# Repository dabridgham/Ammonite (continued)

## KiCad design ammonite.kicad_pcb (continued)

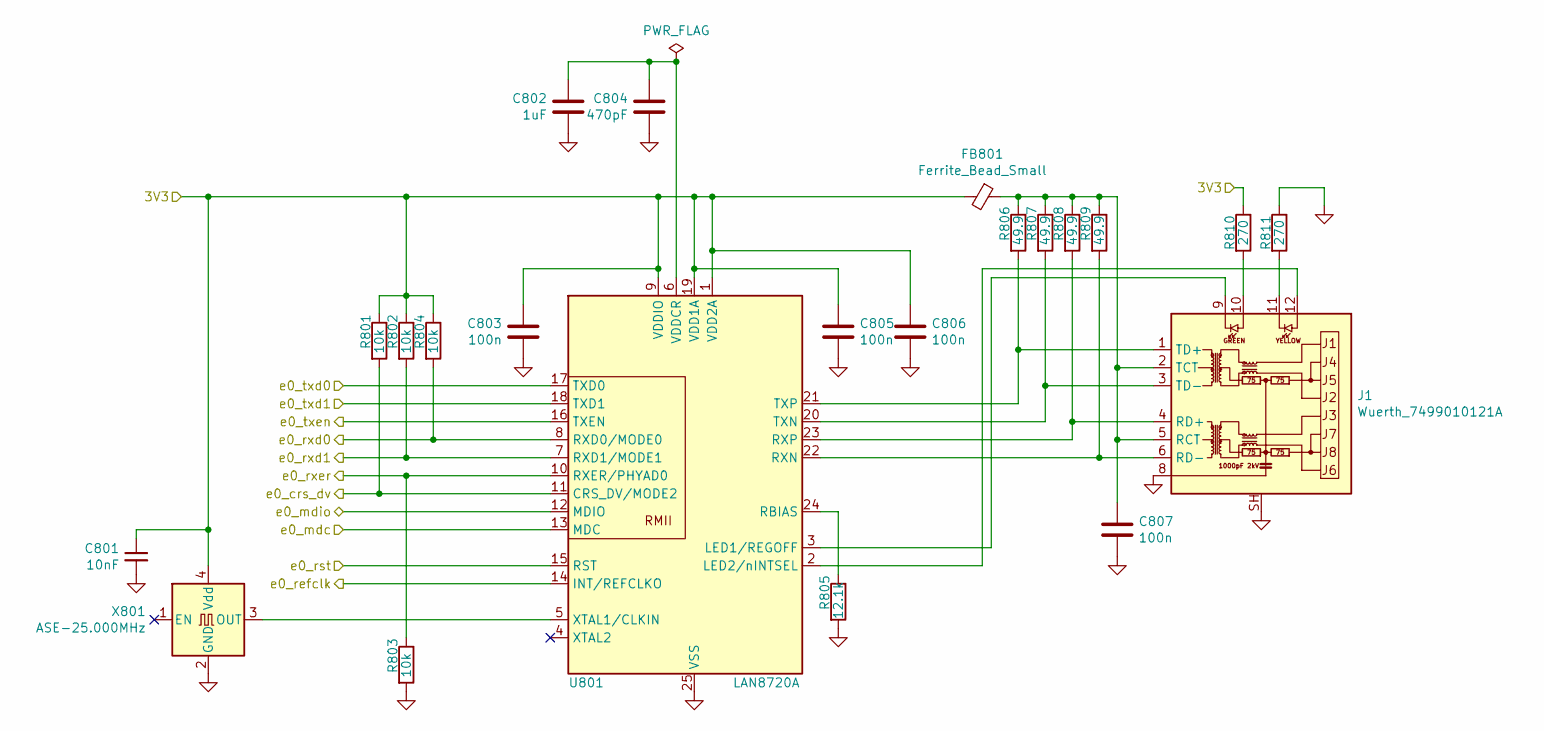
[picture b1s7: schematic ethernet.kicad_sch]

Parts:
C801: 10nF; C_0603_1608Metric
C802: 1uF; C_0603_1608Metric
C803, C805, C806, C807: 100n; C_0603_1608Metric
C804: 470pF; C_0603_1608Metric
FB801: Ferrite_Bead_Small; L_0603_1608Metric
J1: Wuerth_7499010121A; RJ45_Wuerth_7499010121A_Horizontal
R801, R802, R803, R804: 10k; R_0603_1608Metric
R805: 12.1k; R_0603_1608Metric
R806, R807, R808, R809: 49.9; R_0603_1608Metric
R810, R811: 270; R_0603_1608Metric
U801: LAN8720A; QFN-24-1EP_4x4mm_P0.5mm_EP2.6x2.6mm
X801: ASE-25.000MHz; Oscillator_SMD_Abracon_ASE-4Pin_3.2x2.5mm

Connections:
/3V3: C801.1, C803.1, C805.1, C806.1, FB801.2, R801.1, R802.1, R804.1, R810.1, U801.1 (VDD2A), U801.9 (VDDIO), U801.19 (VDD1A), X801.4 (Vdd); also elsewhere on the board
/e0_crs_dv: R801.2, U801.11 (CRS_DV/MODE2); also elsewhere on the board
/e0_mdc: U801.13 (MDC); also elsewhere on the board
/e0_mdio: U801.12 (MDIO); also elsewhere on the board
/e0_refclk: U801.14 (INT/REFCLKO); also elsewhere on the board
/e0_rst: U801.15 (RST); also elsewhere on the board
/e0_rxd0: R804.2, U801.8 (RXD0/MODE0); also elsewhere on the board
/e0_rxd1: R802.2, U801.7 (RXD1/MODE1); also elsewhere on the board
/e0_rxer: R803.1, U801.10 (RXER/PHYAD0); also elsewhere on the board
/e0_txd0: U801.17 (TXD0); also elsewhere on the board
/e0_txd1: U801.18 (TXD1); also elsewhere on the board
/e0_txen: U801.16 (TXEN); also elsewhere on the board
GND: C801.2, C802.2, C803.2, C804.2, C805.2, C806.2, C807.2, J1.8, J1.SH, R803.2, R805.2, R811.1, U801.25 (VSS), X801.2 (GND); also elsewhere on the board
unnamed: C802.1, C804.1, U801.6 (VDDCR)
unnamed: C807.1, FB801.1, J1.2 (TCT), J1.5 (RCT), R806.1, R807.1, R808.1, R809.1
unnamed: J1.1 (TD+), R806.2, U801.21 (TXP)
unnamed: J1.3 (TD-), R807.2, U801.20 (TXN)
unnamed: J1.4 (RD+), R808.2, U801.23 (RXP)
unnamed: J1.6 (RD-), R809.2, U801.22 (RXN)
unnamed: J1.9, U801.3 (LED1/REGOFF)
unnamed: J1.10, R810.2
unnamed: J1.11, R811.2
unnamed: J1.12, U801.2 (LED2/nINTSEL)
unnamed: R805.1, U801.24 (RBIAS)
unnamed: U801.5 (XTAL1/CLKIN), X801.3 (OUT)

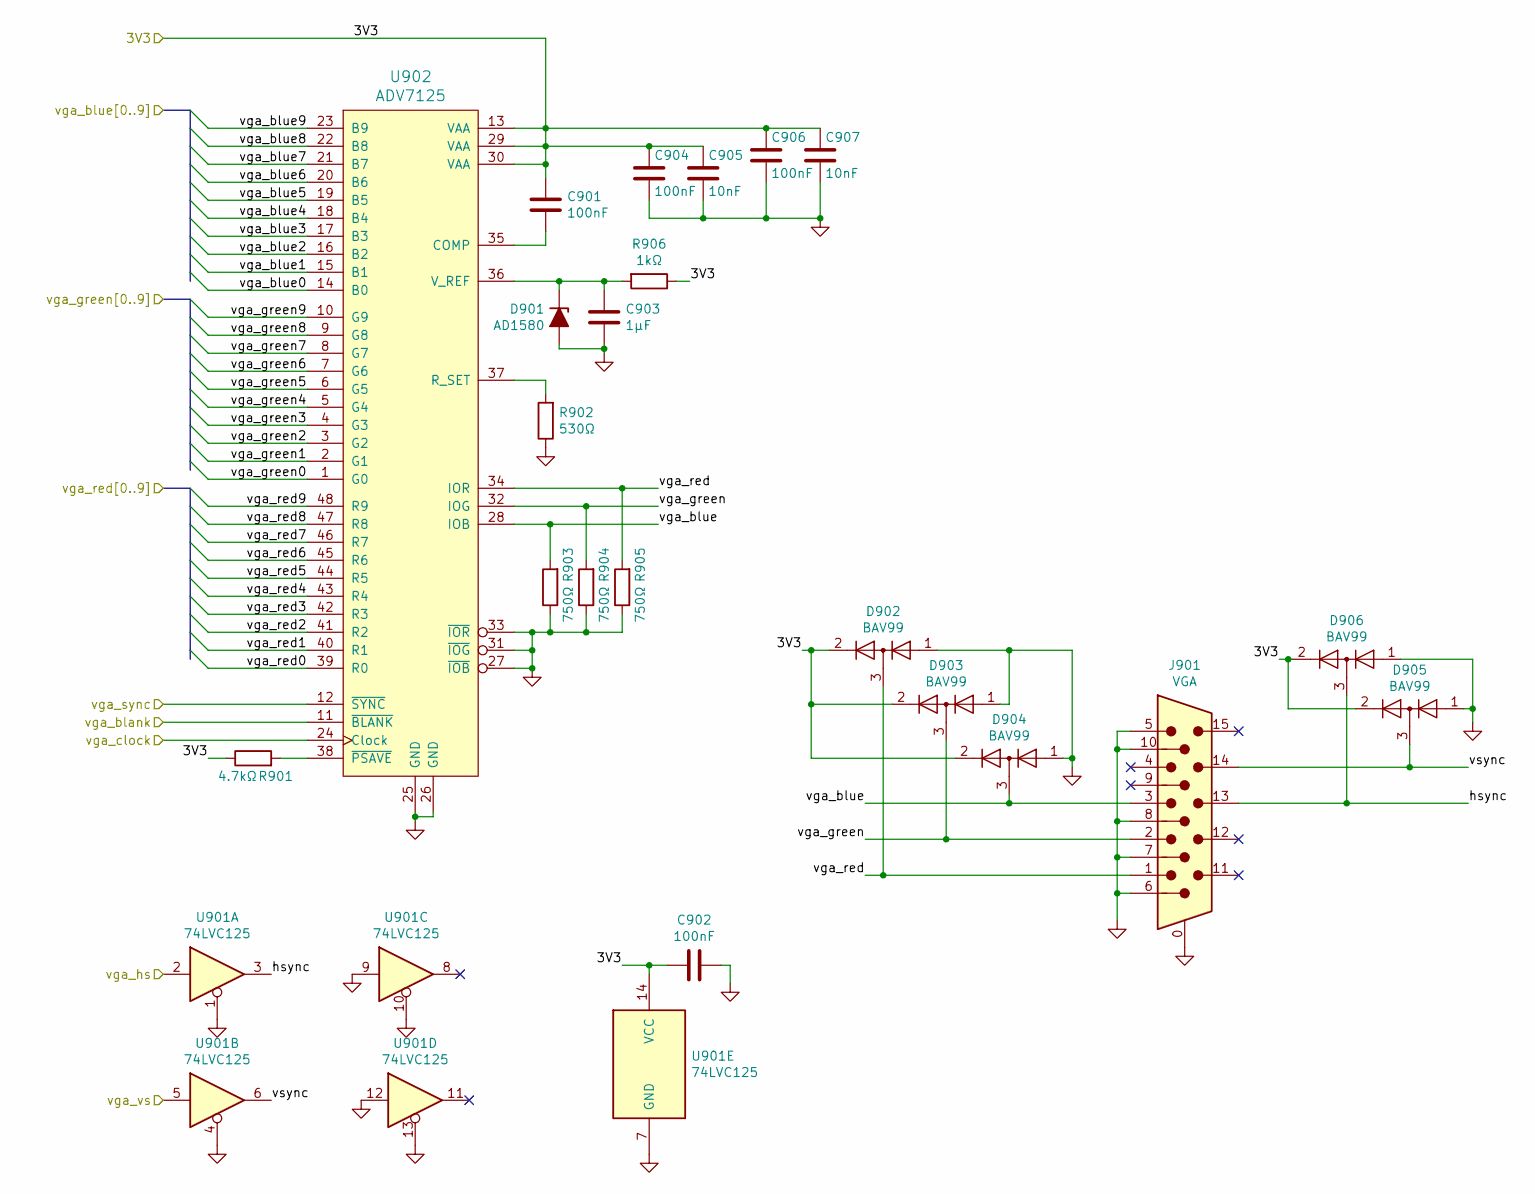
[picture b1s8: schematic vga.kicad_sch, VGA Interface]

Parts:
C901, C902, C904, C906: 100nF; C_0603_1608Metric
C903: 1µF; C_0603_1608Metric
C905, C907: 10nF; C_0603_1608Metric
D901: AD1580; SOT-23
D902, D903, D904, D905, D906: BAV99; SOT-23
J901: VGA; DSUB-15-HD_Female_Horizontal_P2.29x1.98mm_EdgePinOffset8.35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
R901: 4.7kΩ; R_0603_1608Metric
R902: 530Ω; R_0603_1608Metric
R903, R904, R905: 750Ω; R_0603_1608Metric
R906: 1kΩ; R_0603_1608Metric
U901: 74LVC125; TSSOP-14_4.4x5mm_P0.65mm
U902: ADV7125; LQFP-48_7x7mm_P0.5mm

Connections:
/3V3: C901.1, C902.1, C904.1, C905.1, C906.1, C907.1, D902.2 (A), D903.2 (A), D904.2 (A), D905.2 (A), D906.2 (A), R901.1, R906.1, U901.14 (VCC), U902.13 (VAA), U902.29 (VAA), U902.30 (VAA); also elsewhere on the board
/VGA/hsync: D906.3 (K), J901.13, U901.3
/VGA/vga_blue: D904.3 (K), J901.3, R903.2, U902.28 (IOB)
/VGA/vga_green: D903.3 (K), J901.2, R904.2, U902.32 (IOG)
/VGA/vga_red: D902.3 (K), J901.1, R905.2, U902.34 (IOR)
/VGA/vsync: D905.3 (K), J901.14, U901.6
/vga_blank: U902.11 (~BLANK); also elsewhere on the board
/vga_blue0: U902.14 (B0); also elsewhere on the board
/vga_blue1: U902.15 (B1); also elsewhere on the board
/vga_blue2: U902.16 (B2); also elsewhere on the board
/vga_blue3: U902.17 (B3); also elsewhere on the board
/vga_blue4: U902.18 (B4); also elsewhere on the board
/vga_blue5: U902.19 (B5); also elsewhere on the board
/vga_blue6: U902.20 (B6); also elsewhere on the board
/vga_blue7: U902.21 (B7); also elsewhere on the board
/vga_blue8: U902.22 (B8); also elsewhere on the board
/vga_blue9: U902.23 (B9); also elsewhere on the board
/vga_clock: U902.24 (Clock); also elsewhere on the board
/vga_green0: U902.1 (G0); also elsewhere on the board
/vga_green1: U902.2 (G1); also elsewhere on the board
/vga_green2: U902.3 (G2); also elsewhere on the board
/vga_green3: U902.4 (G3); also elsewhere on the board
/vga_green4: U902.5 (G4); also elsewhere on the board
/vga_green5: U902.6 (G5); also elsewhere on the board
/vga_green6: U902.7 (G6); also elsewhere on the board
/vga_green7: U902.8 (G7); also elsewhere on the board
/vga_green8: U902.9 (G8); also elsewhere on the board
/vga_green9: U902.10 (G9); also elsewhere on the board
/vga_hs: U901.2; also elsewhere on the board
/vga_red0: U902.39 (R0); also elsewhere on the board
/vga_red1: U902.40 (R1); also elsewhere on the board
/vga_red2: U902.41 (R2); also elsewhere on the board
/vga_red3: U902.42 (R3); also elsewhere on the board
/vga_red4: U902.43 (R4); also elsewhere on the board
/vga_red5: U902.44 (R5); also elsewhere on the board
/vga_red6: U902.45 (R6); also elsewhere on the board
/vga_red7: U902.46 (R7); also elsewhere on the board
/vga_red8: U902.47 (R8); also elsewhere on the board
/vga_red9: U902.48 (R9); also elsewhere on the board
/vga_sync: U902.12 (~SYNC); also elsewhere on the board
/vga_vs: U901.5; also elsewhere on the board
GND: C902.2, C903.2, C904.2, C905.2, C906.2, C907.2, D901.2 (A), D902.1 (K), D903.1 (K), D904.1 (K), D905.1 (K), D906.1 (K), J901.0, J901.5, J901.6, J901.7, J901.8, J901.10, R902.1, R903.1, R904.1, R905.1, U901.1, U901.4, U901.7 (GND), U901.9, U901.10, U901.12, U901.13, U902.25 (GND), U902.26 (GND), U902.27 (~IOB), U902.31 (~IOG), U902.33 (~IOR); also elsewhere on the board
unnamed: C901.2, U902.35 (COMP)
unnamed: C903.1, D901.1 (K), R906.2, U902.36 (V_REF)
unnamed: R901.2, U902.38 (~PSAVE)
unnamed: R902.2, U902.37 (R_SET)

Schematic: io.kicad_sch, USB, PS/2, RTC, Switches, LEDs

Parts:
BT1001: 3V; TE-1775485
C1001, C1002, C1004, C1005, C1006, C1007, C1011, C1013, C1014: 100nF; C_0603_1608Metric
C1003: 10nF; C_0603_1608Metric
C1008, C1012: 150µF 10V; CP_EIA-6032-28_Kemet-C
C1009, C1010: 1uF; C_0603_1608Metric
D1001, D1002, D1003, D1004, D1005, D1006, D1007, D1008: green; LED_0603_1608Metric
J1001: USB_A; Amphenol_87583_USB_A
J1002: PS/2; MD-60SM
R1001, R1002, R1003: 4.7k; R_0603_1608Metric
R1004: 56.2k; R_0603_1608Metric
R1005, R1006: 100k; R_0603_1608Metric
R1007: 8.06k; R_0603_1608Metric
R1008: 20k; R_0603_1608Metric
R1011, R1012, R1013, R1014: 1k; R_0603_1608Metric
R1016, R1017, R1018, R1019, R1020, R1021, R1022, R1023: 240; R_0603_1608Metric
S1001: Config; SW_DIP_SPSTx08_Slide_6.7x21.88mm_W7.62mm_P2.54mm_LowProfile
U1001: MCP79411; SOIC-8_3.9x4.9mm_P1.27mm
U1002: TPS2561; VSON-10-1EP_3x3mm_P0.5mm_EP1.65x2.4mm_ThermalVias
U1003: USB3340; QFN-32-1EP_5x5mm_Pitch0.5mm
U1004: TXS0104E; TSSOP-14_4.4x5mm_P0.65mm
X1001: ASE-24.000MHz; Oscillator_SMD_Abracon_ASE-4Pin_3.2x2.5mm
Y1001: 32.768kHz; Crystal_SMD_0603-2Pin_6.0x3.5mm

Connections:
/3V3: C1003.1, C1005.1, C1006.1, C1007.1, C1013.2, R1001.1, R1002.1, R1003.1, R1016.1, R1017.1, R1018.1, R1019.1, R1020.1, R1021.1, R1022.1, R1023.1, U1001.8 (Vcc), U1003.8 (REFSEL[0]), U1003.11 (REFSEL[1]), U1003.14 (REFSEL[2]), U1003.21 (VBAT), U1003.32 (VDDIO), U1004.1 (VCCA), U1004.8 (OE), X1001.4 (Vdd); also elsewhere on the board
/5V0: C1004.1, R1005.1, R1006.1, U1002.2 (IN), U1002.3 (IN), U1002.4 (EN1); also elsewhere on the board
/IO/5V_PS2: C1012.1, C1014.1, J1002.3, R1011.1, R1012.1, R1013.1, R1014.1, U1002.9 (OUT1), U1004.14 (VCCB)
/IO/5V_USB: C1008.1, C1011.1, J1001.1 (VBUS), R1008.2, U1002.8 (OUT2)
/kbd_clk: U1004.5 (A4); also elsewhere on the board
/kbd_data: U1004.4 (A3); also elsewhere on the board
/led_0: D1001.1 (K); also elsewhere on the board
/led_1: D1002.1 (K); also elsewhere on the board
/led_2: D1003.1 (K); also elsewhere on the board
/led_3: D1004.1 (K); also elsewhere on the board
/led_4: D1005.1 (K); also elsewhere on the board
/led_5: D1006.1 (K); also elsewhere on the board
/led_6: D1007.1 (K); also elsewhere on the board
/led_7: D1008.1 (K); also elsewhere on the board
/mouse_clk: U1004.2 (A1); also elsewhere on the board
/mouse_data: U1004.3 (A2); also elsewhere on the board
/rtc_mfp: R1003.2, U1001.7 (MFP); also elsewhere on the board
/rtc_scl: R1001.2, U1001.6 (SCL); also elsewhere on the board
/rtc_sda: R1002.2, U1001.5 (SDA); also elsewhere on the board
/sw_0: S1001.9; also elsewhere on the board
/sw_1: S1001.10; also elsewhere on the board
/sw_2: S1001.11; also elsewhere on the board
/sw_3: S1001.12; also elsewhere on the board
/sw_4: S1001.13; also elsewhere on the board
/sw_5: S1001.14; also elsewhere on the board
/sw_6: S1001.15; also elsewhere on the board
/sw_7: S1001.16; also elsewhere on the board
/usb0_d0: U1003.3 (DATA0); also elsewhere on the board
/usb0_d1: U1003.4 (DATA1); also elsewhere on the board
/usb0_d2: U1003.5 (DATA2); also elsewhere on the board
/usb0_d3: U1003.6 (DATA3); also elsewhere on the board
/usb0_d4: U1003.7 (DATA4); also elsewhere on the board
/usb0_d5: U1003.9 (DATA5); also elsewhere on the board
/usb0_d6: U1003.10 (DATA6); also elsewhere on the board
/usb0_d7: U1003.13 (DATA7); also elsewhere on the board
/usb0_dir: U1003.31 (DIR); also elsewhere on the board
/usb0_nxt: U1003.2 (NXT); also elsewhere on the board
/usb0_resetb: U1003.27 (RESETB); also elsewhere on the board
/usb0_stp: U1003.29 (STP); also elsewhere on the board
/usb_clk60: U1003.1 (CLKOUT); also elsewhere on the board
GND: BT1001.2 (-), C1001.1, C1002.1, C1003.2, C1004.2, C1005.2, C1006.2, C1007.2, C1008.2, C1009.2, C1010.2, C1011.2, C1012.2, C1013.1, C1014.2, J1001.4 (GND), J1001.5 (Shield), J1002.4, R1004.2, R1007.2, S1001.1, S1001.2, S1001.3, S1001.4, S1001.5, S1001.6, S1001.7, S1001.8, U1001.4 (GND), U1002.1 (GND), U1002.11 (PAD), U1003.33 (GND), U1004.7 (GND), X1001.2 (GND); also elsewhere on the board
unnamed: BT1001.1 (+), U1001.3 (Vbat)
unnamed: C1001.2, U1001.1 (X1), Y1001.1
unnamed: C1002.2, U1001.2 (X2), Y1001.2
unnamed: C1009.1, U1003.20 (VDD33), U1003.23 (ID)
unnamed: C1010.1, U1003.28 (VDD18)
unnamed: D1001.2 (A), R1016.2
unnamed: D1002.2 (A), R1017.2
unnamed: D1003.2 (A), R1018.2
unnamed: D1004.2 (A), R1019.2
unnamed: D1005.2 (A), R1020.2
unnamed: D1006.2 (A), R1021.2
unnamed: D1007.2 (A), R1022.2
unnamed: D1008.2 (A), R1023.2
unnamed: J1001.2 (D-), U1003.19 (DM)
unnamed: J1001.3 (D+), U1003.18 (DP)
unnamed: J1002.1, R1012.2, U1004.12 (B2)
unnamed: J1002.2, R1013.2, U1004.11 (B3)
unnamed: J1002.5, R1011.2, U1004.13 (B1)
unnamed: J1002.6, R1014.2, U1004.10 (B4)
unnamed: R1004.1, U1002.7 (ILM)
unnamed: R1005.2, U1002.10 (~FAULT1)
unnamed: R1006.2, U1002.6 (~FAULT2)
unnamed: R1007.1, U1003.24 (RBIAS)
unnamed: R1008.1, U1003.22 (VBUS)
unnamed: U1002.5 (EN2), U1003.17 (CPEN)
unnamed: U1003.26 (XI/REFCLK), X1001.3 (OUT)

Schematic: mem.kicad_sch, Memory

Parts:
C15, C16: 22µF 10V; C_0603_1608Metric
C17, C19, C21, C22: 10µF 10V; C_0603_1608Metric
C18: 100nF; C_0603_1608Metric
C20: 220nF; C_0603_1608Metric
R12, R13, R17: 10k; R_0603_1608Metric
R14: 240; R_0603_1608Metric
R15: 89 1%; R_0603_1608Metric
R16: 47k; R_0603_1608Metric
U2: XC7A75T-1CSG324; Xilinx_CSG324
U4: TPS51206; WSON-10-1EP_2x2mm_P0.4mm_EP0.9x1.5mm_ThermalVias
U5: MT41J128M16JT-125; BGA-96_9.0x13.0mm_Layout2x3x16_P0.8mm

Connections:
/1V5: C15.1, C16.1, C21.1, C22.1, U2.A7 (VCCO_35), U2.C3 (VCCO_35), U2.D6 (VCCO_35), U2.F2 (VCCO_35), U2.G5 (VCCO_35), U2.J1 (VCCO_35), U4.1 (VDDQSNS), U5.A1 (VDDQ1), U5.A8 (VDDQ2), U5.B2 (VDD1), U5.C1 (VDDQ3), U5.C9 (VDDQ4), U5.D2 (VDDQ5), U5.D9 (VDD2), U5.E9 (VDDQ6), U5.F1 (VDDQ7), U5.G7 (VDD3), U5.H2 (VDDQ8), U5.H9 (VDDQ9), U5.K2 (VDD4), U5.K8 (VDD5), U5.N1 (VDD6), U5.N9 (VDD7), U5.R1 (VDD8), U5.R9 (VDD9); also elsewhere on the board
/3V3: C17.1, C18.1, R12.2, R13.2, U4.2 (VLDOIN), U4.10 (VDD); also elsewhere on the board
/Memory1/A0: U2.C5 (IO_L1N_T0_AD4N_35), U5.N3 (A0)
/Memory1/A1: U2.B6 (IO_L2N_T0_AD12N_35), U5.P7 (A1)
/Memory1/A2: U2.C7 (IO_L4N_T0_35), U5.P3 (A2)
/Memory1/A3: U2.D5 (IO_L11P_T1_SRCC_35), U5.N2 (A3)
/Memory1/A4: U2.A3 (IO_L8N_T1_AD14N_35), U5.P8 (A4)
/Memory1/A5: U2.E7 (IO_L6P_T0_35), U5.P2 (A5)
/Memory1/A6: U2.A4 (IO_L8P_T1_AD14P_35), U5.R8 (A6)
/Memory1/A7: U2.C6 (IO_L1P_T0_AD4P_35), U5.R2 (A7)
/Memory1/A8: U2.A6 (IO_L3P_T0_DQS_AD5P_35), U5.T8 (A8)
/Memory1/A9: U2.D8 (IO_L4P_T0_35), U5.R3 (A9)
/Memory1/A10: U2.B2 (IO_L10N_T1_AD15N_35), U5.L7 (A10/AP)
/Memory1/A11: U2.A5 (IO_L3N_T0_DQS_AD5N_35), U5.R7 (A11)
/Memory1/A12: U2.B3 (IO_L10P_T1_AD15P_35), U5.N7 (A12/BC#)
/Memory1/A13: U2.B7 (IO_L2P_T0_AD12P_35), U5.T3 (A13)
/Memory1/BA0: U2.E5 (IO_L5N_T0_AD13N_35), U5.M2 (BA0)
/Memory1/BA1: U2.A1 (IO_L9N_T1_DQS_AD7N_35), U5.N8 (BA1)
/Memory1/BA2: U2.E6 (IO_L5P_T0_AD13P_35), U5.M3 (BA2)
/Memory1/CAS#: U2.D3 (IO_L12N_T1_MRCC_35), U5.K3 (CAS#)
/Memory1/CK: R15.2, U2.C4 (IO_L7P_T1_AD6P_35), U5.J7 (CK)
/Memory1/CK#: R15.1, U2.B4 (IO_L7N_T1_AD6N_35), U5.K7 (CK#)
/Memory1/CKE: U2.B1 (IO_L9P_T1_DQS_AD7P_35), U5.K9 (CKE)
/Memory1/DML: U2.G1 (IO_L17N_T2_35), U5.E7 (DML)
/Memory1/DMU: U2.G6 (IO_L19P_T3_35), U5.D3 (DMU)
/Memory1/DQL0: U2.H1 (IO_L17P_T2_35), U5.E3 (DQL0)
/Memory1/DQL1: U2.F1 (IO_L18P_T2_35), U5.F7 (DQL1)
/Memory1/DQL2: U2.E2 (IO_L14P_T2_SRCC_35), U5.F2 (DQL2)
/Memory1/DQL3: U2.E1 (IO_L18N_T2_35), U5.F8 (DQL3)
/Memory1/DQL4: U2.F4 (IO_L13P_T2_MRCC_35), U5.H3 (DQL4)
/Memory1/DQL5: U2.C1 (IO_L16N_T2_35), U5.H8 (DQL5)
/Memory1/DQL6: U2.F3 (IO_L13N_T2_MRCC_35), U5.G2 (DQL6)
/Memory1/DQL7: U2.D2 (IO_L14N_T2_SRCC_35), U5.H7 (DQL7)
/Memory1/DQSL: U2.H2 (IO_L15P_T2_DQS_35), U5.F3 (DQSL)
/Memory1/DQSL#: U2.G2 (IO_L15N_T2_DQS_35), U5.G3 (DQSL#)
/Memory1/DQSU: U2.J4 (IO_L21P_T3_DQS_35), U5.C7 (DQSU)
/Memory1/DQSU#: U2.H4 (IO_L21N_T3_DQS_35), U5.B7 (DQSU#)
/Memory1/DQU0: U2.G4 (IO_L20P_T3_35), U5.D7 (DQU0)
/Memory1/DQU1: U2.H5 (IO_L24N_T3_35), U5.C3 (DQU1)
/Memory1/DQU2: U2.G3 (IO_L20N_T3_35), U5.C8 (DQU2)
/Memory1/DQU3: U2.H6 (IO_L24P_T3_35), U5.C2 (DQU3)
/Memory1/DQU4: U2.J2 (IO_L22N_T3_35), U5.A7 (DQU4)
/Memory1/DQU5: U2.J3 (IO_L22P_T3_35), U5.A2 (DQU5)
/Memory1/DQU6: U2.K1 (IO_L23N_T3_35), U5.B8 (DQU6)
/Memory1/DQU7: U2.K2 (IO_L23P_T3_35), U5.A3 (DQU7)
/Memory1/ODT: U2.F5 (IO_0_35), U5.K1 (ODT)
/Memory1/RAS#: U2.E3 (IO_L12P_T1_MRCC_35), U5.J3 (RAS#)
/Memory1/RESET#: R16.1, U2.J5 (IO_25_35), U5.T2 (RESET#)
/Memory1/VREF15: C20.1, U2.D7 (IO_L6N_T0_VREF_35), U2.F6 (IO_L19N_T3_VREF_35), U4.6 (VTTREF), U5.H1 (VREFDQ), U5.M8 (VREFCA)
/Memory1/WE#: U2.D4 (IO_L11N_T1_SRCC_35), U5.L3 (WE#)
GND: C15.2, C16.2, C17.2, C18.2, C19.2, C20.2, C21.2, C22.2, R14.2, R16.2, R17.1, U4.4 (PGND), U4.8 (GND), U4.11 (PowerPad), U5.A9 (VSS1), U5.B1 (VSSQ1), U5.B3 (VSS2), U5.B9 (VSSQ2), U5.D1 (VSSQ3), U5.D8 (VSSQ4), U5.E1 (VSS3), U5.E2 (VSSQ5), U5.E8 (VSSQ6), U5.F9 (VSSQ7), U5.G1 (VSSQ8), U5.G8 (VSS4), U5.G9 (VSSQ9), U5.J2 (VSS5), U5.J8 (VSS6), U5.L2 (CS#), U5.M1 (VSS7), U5.M9 (VSS8), U5.P1 (VSS9), U5.P9 (VSS10), U5.T1 (VSS11), U5.T9 (VSS12); also elsewhere on the board
unnamed: C19.1, R17.2, U4.3 (VTT), U4.5 (VTTSNS)
unnamed: R12.1, U4.9 (S5)
unnamed: R13.1, U4.7 (S3)
unnamed: R14.1, U5.L8 (ZQ)

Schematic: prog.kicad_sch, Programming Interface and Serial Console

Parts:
C23, C24, C28, C29, C32, C33, C34, C35, C36, C37, C38: 100nF; C_0603_1608Metric
C25, C31: 4.7µF 6.3V; C_0603_1608Metric
C26, C27: 8pF; C_0603_1608Metric
C30: 3.3µF 6.3V; C_0603_1608Metric
D2: green; LED_0603_1608Metric
FB1, FB2: 220Ω @ 100MHz 40mΩ; L_0805_2012Metric
J2: USB_microB; USB_Micro-B_Molex_47346-0001
R18, R19, R21: 10k; R_0603_1608Metric
R20: 2.2k; R_0603_1608Metric
R22: 12k 1%; R_0603_1608Metric
R23: 1k; R_0603_1608Metric
R24: 240; R_0603_1608Metric
U6: 93LC46C-I/MC; DFN-8-1EP_3x2mm_P0.5mm_EP1.75x1.45mm
U7: FT2232HQ; QFN-64-1EP_9x9mm_P0.5mm_EP4.35x4.35mm_ThermalVias
Y1: 12 MHz; Crystal_SMD_Abracon_ABM10-4Pin_2.5x2.0mm

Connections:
/3V3: C23.2, C29.1, C35.1, C36.1, C37.1, C38.1, D2.2 (A), FB1.2, FB2.2, R18.1, R19.1, R21.1, R23.2, U6.6 (ORG), U6.8 (VCC), U7.20 (VCCIO), U7.31 (VCCIO), U7.42 (VCCIO), U7.50 (VREGIN), U7.56 (VCCIO); also elsewhere on the board
/Programming/D+: J2.3 (D+), U7.8 (D+)
/Programming/D-: J2.2 (D-), U7.7 (D-)
/Programming/vcore: C30.1, C32.1, C33.1, C34.1, U7.12 (VCORE), U7.37 (VCORE), U7.49 (VREGOUT), U7.64 (VCORE)
/RXD: U7.39 (BDBUS1); also elsewhere on the board
/TCK: U7.16 (ADBUS0); also elsewhere on the board
/TDI: U7.17 (ADBUS1); also elsewhere on the board
/TDO: U7.18 (ADBUS2); also elsewhere on the board
/TMS: U7.19 (ADBUS3); also elsewhere on the board
/TXD: U7.38 (BDBUS0); also elsewhere on the board
/~CTS: U7.41 (BDBUS3); also elsewhere on the board
/~DCD: U7.45 (BDBUS6); also elsewhere on the board
/~DSR: U7.44 (BDBUS5); also elsewhere on the board
/~DTR: U7.43 (BDBUS4); also elsewhere on the board
/~RI: U7.46 (BDBUS7); also elsewhere on the board
/~RTS: U7.40 (BDBUS2); also elsewhere on the board
GND: C23.1, C24.2, C25.2, C26.1, C27.1, C28.2, C29.2, C30.2, C31.2, C32.2, C33.2, C34.2, C35.2, C36.2, C37.2, C38.2, J2.5 (GND), J2.6 (Shield), R22.2, U6.5 (GND), U7.1 (GND), U7.5 (GND), U7.10 (AGND), U7.11 (GND), U7.13 (TEST), U7.15 (GND), U7.25 (GND), U7.35 (GND), U7.47 (GND), U7.51 (GND), U7.65 (EP); also elsewhere on the board
unnamed: C24.1, C25.1, FB2.1, U7.4 (VPHY)
unnamed: C26.2, U7.2 (OSCI), Y1.3
unnamed: C27.2, U7.3 (OSCO), Y1.1
unnamed: C28.1, C31.1, FB1.1, U7.9 (VPLL)
unnamed: D2.1 (K), R24.1
unnamed: R18.2, R20.2, U6.4 (DO)
unnamed: R19.2, U6.1 (CS), U7.63 (EECS)
unnamed: R20.1, U6.3 (DI), U7.61 (EEDATA)
unnamed: R21.2, U6.2 (SCLK), U7.62 (EECLK)
unnamed: R22.1, U7.6 (REF)
unnamed: R23.1, U7.14 (~RESET)
unnamed: R24.2, U7.54 (BCBUS3), U7.55 (BCBUS4)

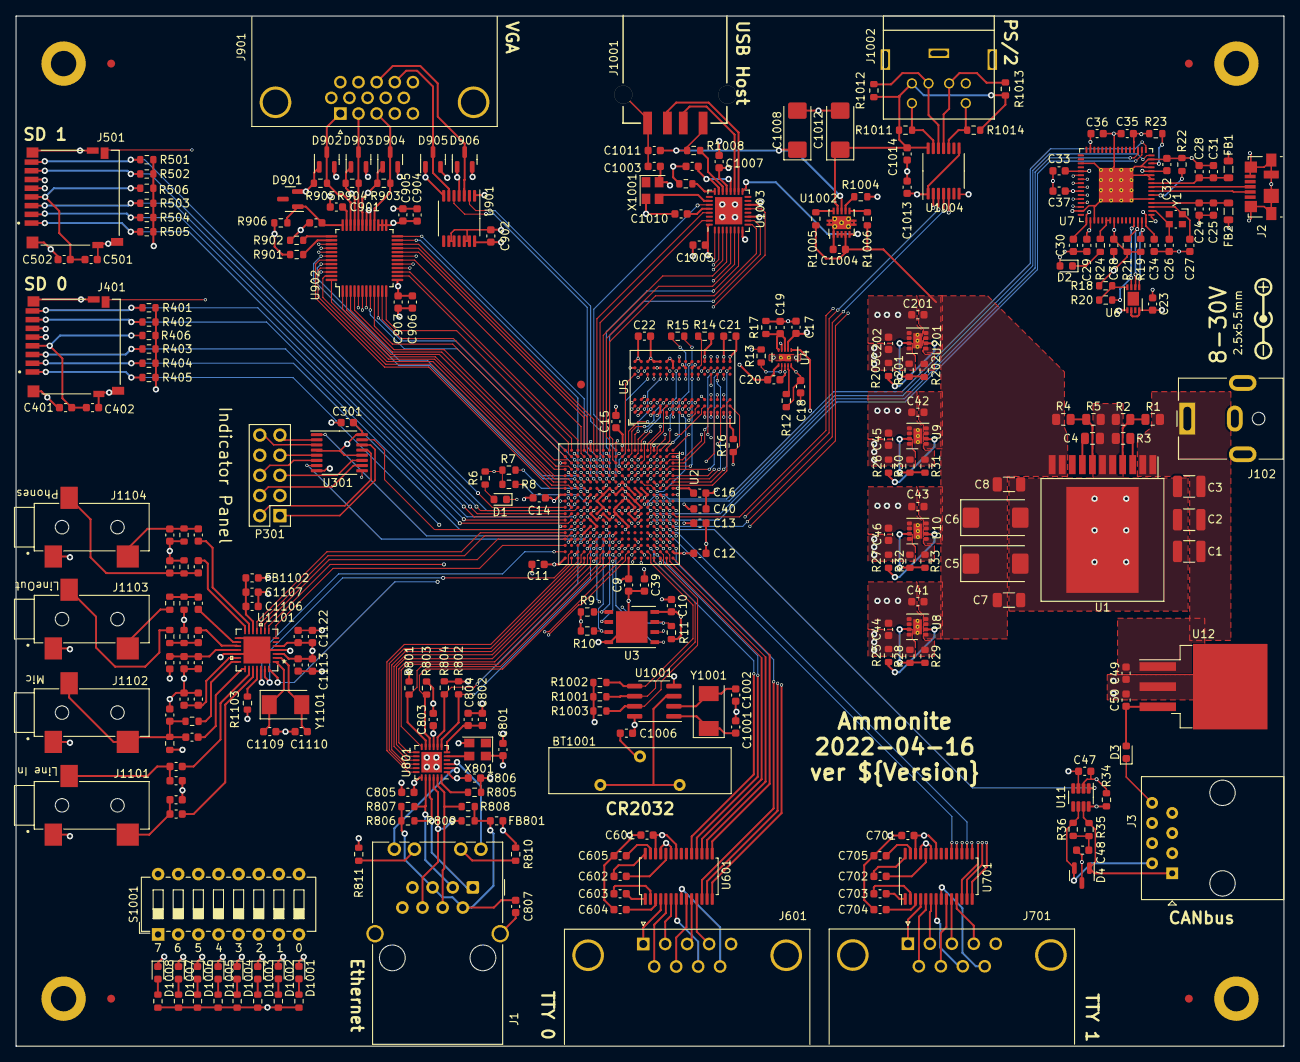
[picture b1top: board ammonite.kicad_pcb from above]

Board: 6 copper layers, 160.0 x 130.0 mm, 295 parts (0 on the bottom side), 349 nets.

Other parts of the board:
C501, C701, C702, C703, C704, C705: 100nF; C_0603_1608Metric
C502: 22uF; C_0603_1608Metric
FID101, FID102, FID103, FID104, FID105: Fiducial; Fiducial_1mm_Mask3mm
J501: Micro_SD_Card_Det; AMPHENOL_1140084168
J701: RS232; DSUB-9_Male_Horizontal_P2.77x2.84mm_EdgePinOffset9.90mm_Hou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
R501, R502, R503, R504, R505: 50k; R_0603_1608Metric
R506: 4.7; R_0603_1608Metric
U701: MAX3243; TSSOP-28_4.4x9.7mm_P0.65mm

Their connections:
/3V3: C701.1, R501.1, R502.1, R503.1, R504.1, R505.1, R506.2, U701.22 (~SHUTDOWN), U701.26 (Vcc); also elsewhere on the board
/sd1_clk: J501.5 (CLK); also elsewhere on the board
/sd1_cmd: J501.3 (CMD), R503.2; also elsewhere on the board
/sd1_dat0: J501.7 (DAT0), R502.2; also elsewhere on the board
/sd1_dat1: J501.8 (DAT1), R501.2; also elsewhere on the board
/sd1_dat2: J501.1 (DAT2), R505.2; also elsewhere on the board
/sd1_dat3: J501.2 (DAT3/CD), R504.2; also elsewhere on the board
/sd1_det: J501.10 (DET_A); also elsewhere on the board
/tty1_cts: U701.15 (R5out); also elsewhere on the board
/tty1_dcd: U701.17 (R3out); also elsewhere on the board
/tty1_dsr: U701.16 (R4out); also elsewhere on the board
/tty1_dtr: U701.13 (T2in); also elsewhere on the board
/tty1_ri: U701.18 (R2out); also elsewhere on the board
/tty1_rts: U701.12 (T3in); also elsewhere on the board
/tty1_rxd: U701.19 (R1out); also elsewhere on the board
/tty1_txd: U701.14 (T1in); also elsewhere on the board
GND: C501.2, C502.2, C701.2, C704.2, C705.2, J501.6 (VSS), J501.9 (DET_B), J501.11 (SHIELD), J701.0 (PAD), J701.5, U701.23 (~ONLINE), U701.25 (GND); also elsewhere on the board
unnamed: C501.1, C502.1, J501.4 (VDD), R506.1
unnamed: C702.1, U701.28 (C1+)
unnamed: C702.2, U701.24 (C1-)
unnamed: C703.1, U701.1 (C2+)
unnamed: C703.2, U701.2 (C2-)
unnamed: C704.1, U701.3 (V-)
unnamed: C705.1, U701.27 (V+)
unnamed: J701.1, U701.4 (R1in)
unnamed: J701.2, U701.6 (R3in)
unnamed: J701.3, U701.10 (T2out)
unnamed: J701.4, U701.11 (T3out)
unnamed: J701.6, U701.5 (R2in)
unnamed: J701.7, U701.9 (T1out)
unnamed: J701.8, U701.7 (R4in)
unnamed: J701.9, U701.8 (R5in)

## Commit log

2022-10-15 Initial import of files into git.
2022-10-15 Added README
2022-10-15 Added ammonite.kicad_pro and ammonite.kicad_pcb
